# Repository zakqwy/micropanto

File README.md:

# MicroPanto

MicroPanto is a 50:1 pantograph reducer that converts a desktop CNC router into a micro-engraver. The machine is driven by a [Handibot](https://www.shopbottools.com/products/handibot), whose working range is shrunk to a few millimeters with a corresponding increase in resolution. A microswitch temporarily mounted to the Handibot's Z-axis actuates a stylus which can be electronically adjusted for different workpiece heights. The working tool is a laser-turned diamond bonded to a strip of stainless shim stock with a tip radius of roughly 2 microns. After assembling the machine at Haystack, a number of substrates (polished stone, steel, obsidian, gold-coated glass, silver, rice, etc) were micro-engraved with tiny messages and designs.

[project video link](https://player.vimeo.com/video/579890845) (thanks Jack!)

[a more detailed engraving video](https://youtu.be/u6EFz45_r_Y)

_Machine temporarily installed in the Haystack Metal Shop:_

_"Too Many Potatoes" engraved on a gold-coated slide, with 1/64" end mill for scale:_

_Stylus end showing base plate, work in vise, servo for stylus actuation, stylus control PCB, and modular superelastic flexure linkages:_

This work may be reproduced, modified, distributed, performed, and displayed for any purpose, but must acknowledge the orginal project. Copyright is retained and must be preserved. The work is provided as is; no warranty is provided, and users accept all liability.

© zach fredin, massachusetts institute of technology, 2021

## micro-engraving
We tried micro-engraving a number of different things at Haystack. Here is a summary:

|thing|notes|
|---|---|
|gold-coated glass slide|Worked fairly well if stylus pressure was adjusted properly. Delicate during handling, somewhat impractical.|
|polished stone|Sourced from Ellen's collection (thanks Ellen!). Maybe picture jasper? Engraved fairly well, a bit of chipping if pressure too high. Required inking to see marks.|
|obsidian|Chips quite a bit. Looks promising if pressure can be better controlled; not great as-is.|
|aluminum|Snapped the diamond off the stylus! Likely an epoxy problem rather than a material issue; diamond re-affixed with CA and no further breakages.|
|silver|Looks _great_, especially if silver is polished and patinaed prior to marking.|
|black oxide coated steel|Tested on a few pairs of parallel-jaw pliers. Looks good, excellent detail.|
|pearl|Roundness is challenging. Needs careful pressure control to avoid over-engraving. Not great with current stylus design.|
|dry rice|Shockingly good, but did require inking afterwards. Maybe the marks would pick up extra staining in a pilaf and become visible (and stay edible)?|
|painted steel|i.e Zach's new glasses frames. Worked fairly well, paint was a bit thick which affected resolution. Underlying scratches on steel base are probably quite fine.|
|brushed stainless|Excellent detail; difficult to see.|

Perhaps not surprisingly, the 50:1 reduction ratio combined with my hesitency to push the machine's working range meant many of the engravings were quite difficult to see, even with a 10x loupe. Neil brought a cheap electronic microscope which I photographed; in retrospect, I should have found a micro SD card and pulled images directly off the instrument. Jack also got a few pictures with his amazing macro lens setup. As I find time, I'll use our instruments at CBA to get better images and update the gallery below.

_"The Center for Bits 'n Atoms", poorly mouse-drawn on the Handibot's SmoothSketch App:_

_The resulting engraving on polished stone, after inking to add contrast. The "o" in Atoms is roughly 100 microns in diameter, the same as a typical strand of hair:_

_"Too Many Potatoes" rendered in inked stone:_

_One of Andrea Dezsö's Forest Beings in gold-coated glass:_

_... and again in inked stone:_

_... and finally on grains of inked rice, along with a "HAYSTACK" sign:_

_A Haystack welcome message (and another CBA "logo") in inked stone:_

_Lauren Fensterstock's black hole drawing, later micro-engraved on a number of substrates:_

_Black hole rendered on parallel-jaw pliers, with scale bar:_

_Zoomed out black hole for reference:_

_"Too Many Potatoes" on my new glasses frames, without magnification to show scale:_

## machine design
More information forthcoming... for now, [ecad](ecad) for the stylus control PCB, [firmware](firmware) for the stylus control firmware, and [mcad](mcad) for the mechanical design files. Parts are fabricated as follows:

|part|method|
|---|---|
|aluminum structural parts|waterjet, drill press|
|nitinol flexures|wire-EDM|
|stylus flexure|laser micro-machining|
|diamond stylus|laser micro-turning|
|PCB|desktop router, soldering iron|
|gold-coated slides|sputter coater|
|slide case|FDM 3D printer|
|pulltruded CFRP tubes|purchased|
|final machine assembly|taper ream, ball-peen hammer, epoxy|

The machine is built from modular superelastic flexures, a concept I developed as part of a class last semester. You can read a lot more about them [here](https://fab.cba.mit.edu/classes/865.21/people/zach/index.html). 

_Stylus detail, showing diamond in down position:_

_Final assembly starts with taper-reaming the waterjetted aluminum parts to match the nitinol flexures:_

_Once prepared, the joints are assembled by tapping in 7/0 taper pins with a ball peen hammer:_

_Disassembled stylus flexure and diamond (near tweezer tip) after breakage due to adhesive failure. Re-secured with cyanoacrylate, which worked well:_

_SEM micrograph of laser-turned diamond stylus, showing rough cut overall shape and finish pass at tip:_

_Another micrograph of the tip of the diamond, showing ~2 um tip radius. Would be worth re-imaging a used tip to see how it wears when used on different substrates:_

MicroPanto roughly consists of:

|item|qty|
|---|---|
|aluminum plate, 1/2"|~75 x 75 mm|
|aluminum plate, 1/4"|~150 x 150 mm|
|aluminum plate, 1/16"|~10 x 80 mm|
|8 mm pulltruded CFRP tube|qty 3, 1 m|
|superelastic nitinol, 10 mm|~1 cc|
|bolts|~10?|
|7/0 taper pins|10|
|FR1 PCB stock|~75 x 50 mm|
|single-crystal CVD diamond|~1 x 1 x 3 mm|
|250 um stainless sheet|~10 x 40 mm|
|4 mm dowel pin|1|
|small servo motor|1|
|cable|~3 m|
|limit switch|1|
|Handibot|1|
|ATtiny412 + support components|1|
|computer|1|
|1/4" x 1/4" magnets|2|
|epoxy|a few packets|
|cable loom (for CFRP splinter protection)|~3 m|
|1/4" shaft stock|~100 mm|
|tiny vise|1|

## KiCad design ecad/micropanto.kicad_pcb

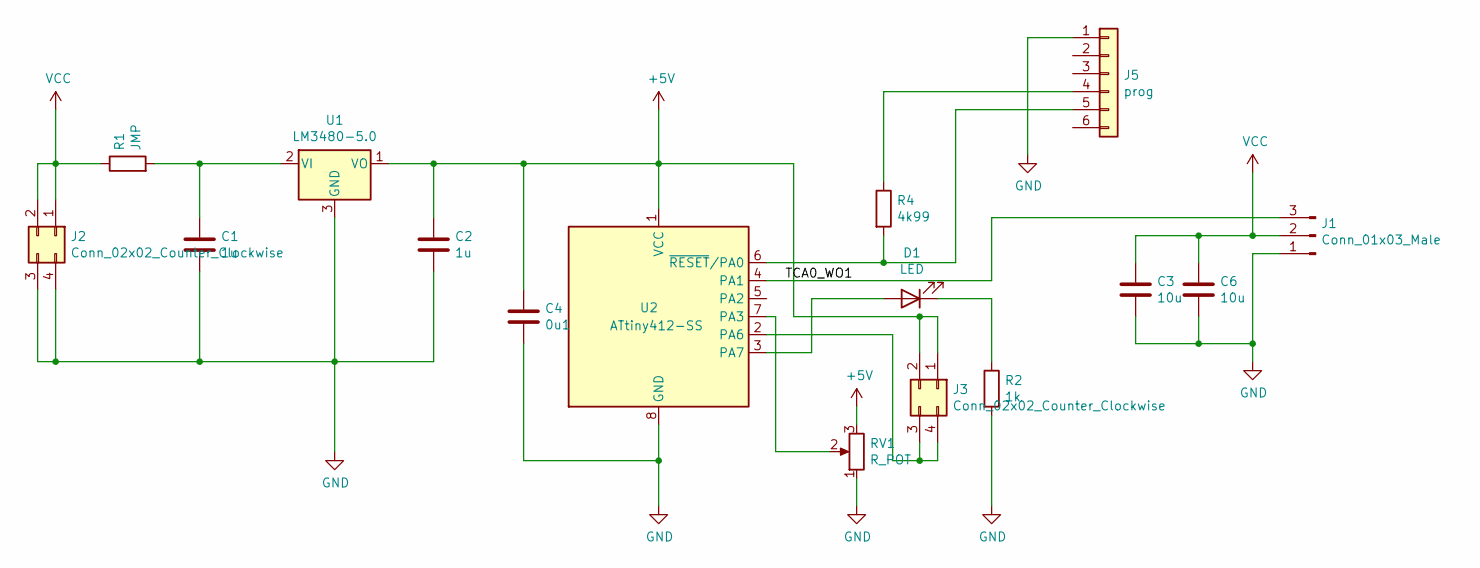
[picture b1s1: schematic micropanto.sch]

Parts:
C1, C2: 1u; fab_C_1206
C3, C6: 10u; fab_R_1206
C4: 0u1; fab_C_1206
D1: LED; fab_LED_1206
J1: Conn_01x03_Male; CONN_SERVO_SMT
J2, J3: Conn_02x02_Counter_Clockwise; PinHeader_2x02_P2.54mm_Vertical_SMD
J5: prog; fab_CONN_1x06_SMD
R1: JMP; fab_R_1206
R2: 1k; fab_R_1206
R4: 4k99; fab_R_1206
RV1: R_POT; Potentiometer_Bourns_3214G_Horizontal
U1: LM3480-5.0; fab_SMD_SOT23
U2: ATtiny412-SS; fab_IC_SOIC8

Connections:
+5V: C2.1, C4.1, J3.1, J3.2, RV1.3, U1.1 (VO), U2.1 (VCC)
/TCA0_WO1: J1.3, U2.4 (PA1)
GND: C1.2, C2.2, C3.2, C4.2, C6.2, J1.1, J2.3, J2.4, J5.1, R2.2, RV1.1, U1.3 (GND), U2.8 (GND)
unnamed: C1.1, R1.2, U1.2 (VI)
unnamed: D1.1 (K), R2.1
unnamed: D1.2 (A), U2.3 (PA7)
unnamed: J3.3, J3.4, U2.2 (PA6)
unnamed: J5.4, R4.1
unnamed: J5.5, R4.2, U2.6 (~RESET~/PA0)
unnamed: RV1.2, U2.7 (PA3)
VCC: C3.1, C6.1, J1.2, J2.1, J2.2, R1.1

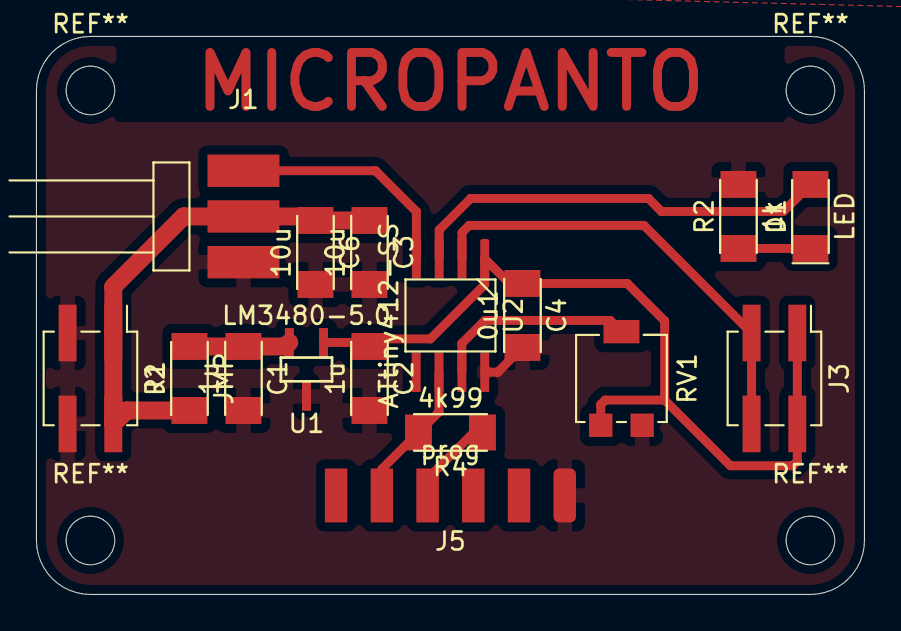
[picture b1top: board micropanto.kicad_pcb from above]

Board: 2 copper layers, 46.0 x 31.0 mm, 16 parts (0 on the bottom side), 11 nets.

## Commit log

2023-03-24 mirror https://gitlab.cba.mit.edu/zfredin/micropanto
